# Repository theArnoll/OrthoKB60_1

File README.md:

# Arnoll OrthoKB60 1

A non-QWERTY-friendly 100% orthorlinear keyboard
65 Key 60% ortholinear keyboard

## Layout and instruction

.: + `E`: ex. `A` + `E` = ä (Alt code for Windows, Option code in Mac Layer)  
+: `fn`: ex. `Home | +Pgup` means `fn` + `Home` = `Page up`  
/: `fn2`: ex: `Caps | /⇧Home` means `fn2` + `Caps` = "`Shift` + `Home`"  
`fn2` = `fn` + `Left`  
`[ | /F11 | + Vol-`: `[` = `[`, `fn` + `[` = Volume +, `fn2` + `[` = `F11`

Keys that the text is not black and in the same color next to each other act as the same key as the right key (left key + right key = right key)  
Ex. ] + Backspace = Backspace, End + Enter = Enter

Keypad layer (At fn+U): Other keys are transparent but LAlt becomes RAlt, so if wanted to RAlt + KP, just switch to keypad layer and type Alt + Keypad numbers.

## Development Stage

- [x] IO definition ([.overlay](./boards/shields/arnoll_orthokb60_1/arnoll_orthokb60_1.overlay))
  - Column: `&shifter` 0~15 (8 and 9 excluded) which `cs-gpio` is `&xiao_d 5`
  - Row: `&xiao_d` 4~0
- [x] RC() transform ([.overlay](./boards/shields/arnoll_orthokb60_1/arnoll_orthokb60_1.overlay))
- [x] physical layout and position_map layout ([.overlay](./boards/shields/arnoll_orthokb60_1/arnoll_orthokb60_1.overlay))
- [ ] Keymap
  - Layers
    - (0) Main layer (&kp Q &kp W, ...)
    - (1) Mac Main layer (* mac fn / &kp GLOBE)
    - (2) Hardware Dvorak layer (&kp SQT &kp COMMA &kp DOT &kp P, ...)
    - (3) fn layer
    - (4) Mac fn layer
    - (5) fn2 layer
    - (6) Numpad layer
    - (7~9) Leave custom layer 1~3
- [ ] AE, OE, UE, ES
- [ ] Caps, Number Lock, macLock indicator
- [ ] Leave Linux and cross-platform umlaut solution and 3 extra layers for ZMK customization
  - fn2 + L = Linux Layer?

## To experiment

https://zmk.dev/docs/keymaps/list-of-keycodes#editing

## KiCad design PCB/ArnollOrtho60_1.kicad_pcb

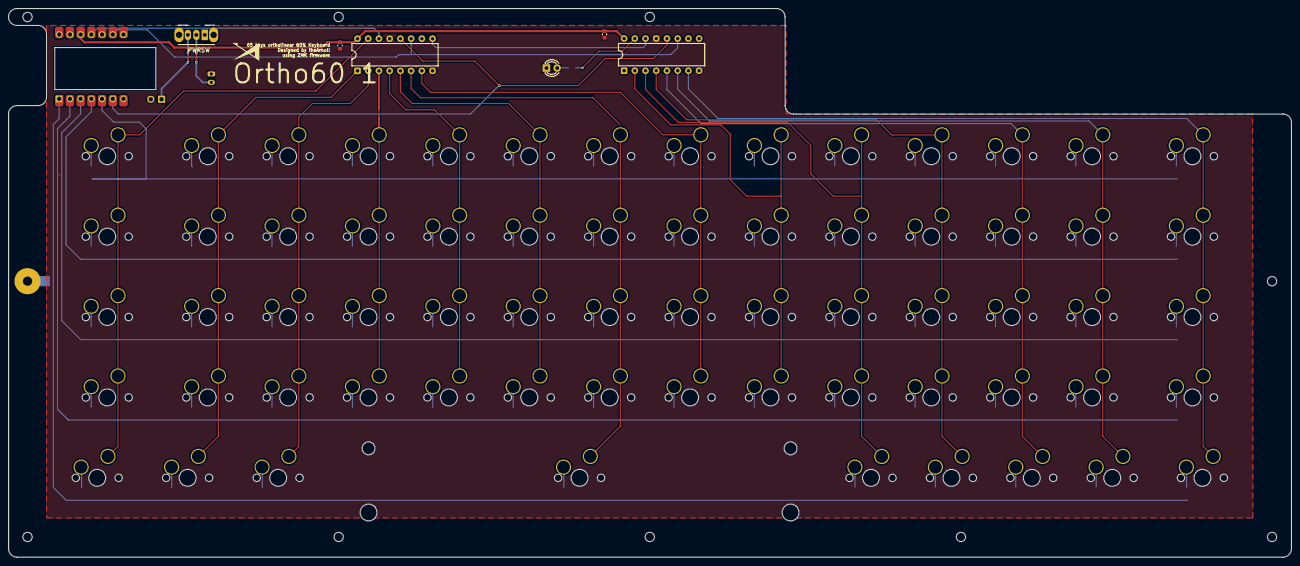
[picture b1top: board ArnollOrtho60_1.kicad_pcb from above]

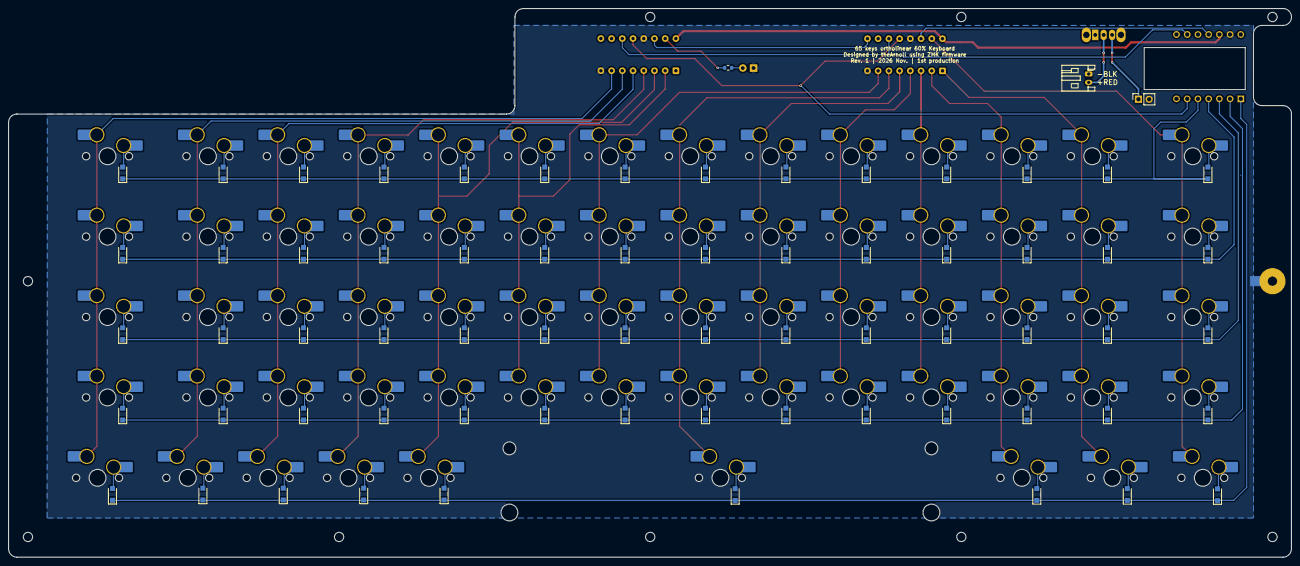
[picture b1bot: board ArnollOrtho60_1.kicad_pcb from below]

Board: 2 copper layers, 304.0 x 130.0 mm, 74 parts (68 on the bottom side), 6 nets.

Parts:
0.1uF, 0.1uF#2: C_0603_1608Metric
74595, 74595#2: DIP-16_W7.62mm
BAT: JST_PH_S2B-PH-K_1x02_P2.00mm_Horizontal
Batt-XIAO: PinSocket_1x02_P2.54mm_Vertical
Diode, Diode1, Diode2, Diode3, Diode4, Diode5, Diode6, Diode7, Diode8, Diode9, Diode10, Diode11, Diode11#2, Diode11#3, Diode12, Diode13, Diode14, Diode15, Diode16, Diode17, Diode18, Diode19, Diode20, Diode21, Diode22, Diode23, Diode24, Diode25, Diode26, Diode27, Diode28, Diode29, Diode30, Diode31, Diode32, Diode33, Diode34, Diode35, Diode36, Diode36#2, Diode36#3, Diode36#4, Diode37, Diode38, Diode39, Diode40, Diode41, Diode42, Diode43, Diode44, Diode44#2, Diode44#3, Diode44#4, Diode45, Diode46, Diode47, Diode48, Diode48#2, Diode49, Diode49#2, Diode50, Diode50#2, Diode51, Diode52, Diode53: Nexperia_CFP3_SOD-123W
LED: LED_D3.0mm
PWRSW: SW_Slide_SPDT_Angled_CK_OS102011MA1Q
R_LED: R_0603_1608Metric

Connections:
595Clock: 74595.11, 74595#2.11
595Data: 74595.9, 74595.14, 74595#2.14
595Latch: 74595.12, 74595#2.12
BAT+: BAT.2, Batt-XIAO.1, PWRSW.2, PWRSW.3
GND: 0.1uF.2, 0.1uF#2.2, 74595.8, 74595.13, 74595#2.8, 74595#2.13, BAT.1, Batt-XIAO.2, LED.1
Vcc: 0.1uF.1, 0.1uF#2.1, 74595.10, 74595.16, 74595#2.10, 74595#2.16

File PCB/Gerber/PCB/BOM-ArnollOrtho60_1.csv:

Comment,Designator,Footprint,LCSC,Quantity
MX_1.00u_PG151101S11,"REF**,REF**1,REF**10,REF**11,REF**12,REF**13,REF**14,REF**15,REF**16,REF**17,REF**18,REF**19,REF**2,REF**20,REF**21,REF**22,REF**23,REF**24,REF**25,REF**26,REF**27,REF**28,REF**29,REF**3,REF**30,REF**31,REF**32,REF**33,REF**34,REF**35,REF**36,REF**37,REF**38,REF**39,REF**4,REF**40,REF**41,REF**42,REF**43,REF**44,REF**45,REF**46,REF**47,REF**5,REF**6,REF**7,REF**8,REF**9",MX_Hotswap_1.00u,C49352235,48
Nexperia_CFP3_SOD-123W,"Diode,Diode1,Diode10,Diode11,Diode12,Diode13,Diode14,Diode15,Diode16,Diode17,Diode18,Diode19,Diode2,Diode20,Diode21,Diode22,Diode23,Diode24,Diode25,Diode26,Diode27,Diode28,Diode29,Diode3,Diode30,Diode31,Diode32,Diode33,Diode34,Diode35,Diode36,Diode37,Diode38,Diode39,Diode4,Diode40,Diode41,Diode42,Diode43,Diode44,Diode45,Diode46,Diode47,Diode48,Diode49,Diode5,Diode50,Diode51,Diode52,Diode53,Diode6,Diode7,Diode8,Diode9",Nexperia_CFP3_SOD-123W,C81598,54
PinSocket_1x02_P2.54mm_Vertical,Batt-XIAO,PinSocket_1x02_P2.54mm_Vertical,,1
DIP-16_W7.62mm,74595,DIP-16_W7.62mm,,1
R_0603_1608Metric,R_LED,R_0603_1608Metric,,1
LED_D3.0mm,LED,LED_D3.0mm,,1
C_0603_1608Metric,0.1uF,C_0603_1608Metric,,1
JST_PH_S2B-PH-K_1x02_P2.00mm_Horizontal,BAT,JST_PH_S2B-PH-K_1x02_P2.00mm_Horizontal,,1
